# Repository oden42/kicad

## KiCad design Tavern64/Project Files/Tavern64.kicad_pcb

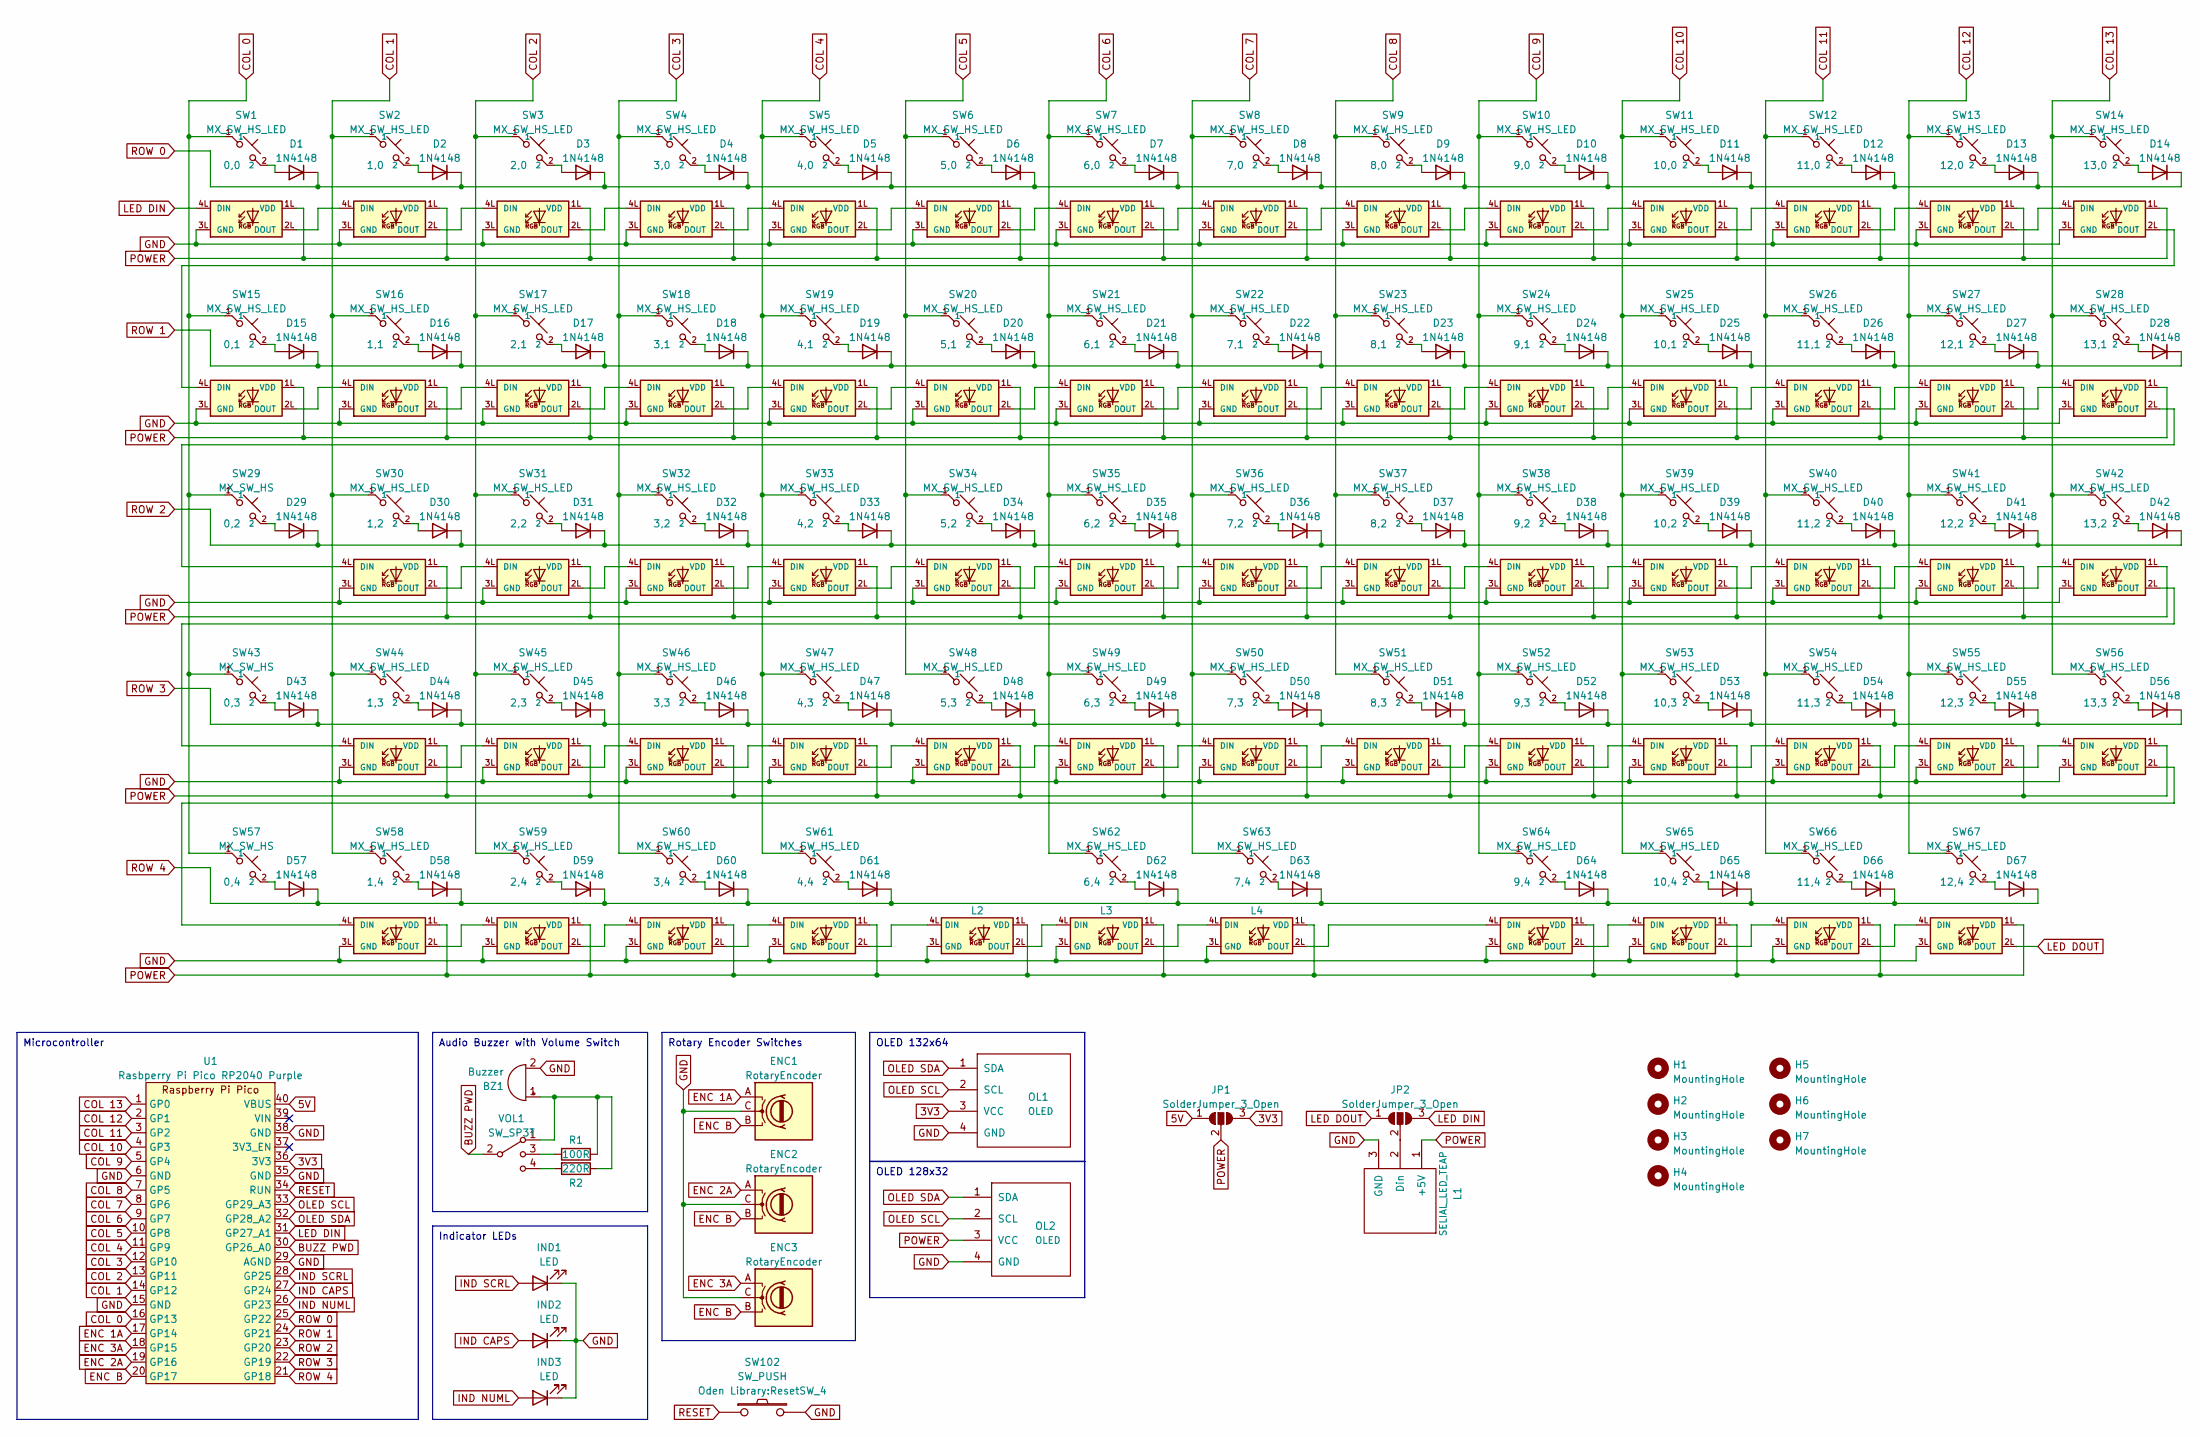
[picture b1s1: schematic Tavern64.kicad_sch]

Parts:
BZ1: Buzzer; Buzzer 8530
D1, D2, D3, D4, D5, D6, D7, D8, D9, D10, D11, D12, D13, D14, D15, D16, D17, D18, D19, D20, D21, D22, D23, D24, D25, D26, D27, D28, D29, D30, D31, D32, D33, D34, D35, D36, D37, D38, D39, D40, D41, D42, D43, D44, D45, D46, D47, D48, D49, D50, D51, D52, D53, D54, D55, D56, D57, D58, D59, D60, D61, D62, D63, D64, D65, D66, D67: 1N4148; Diode-dual
ENC1, ENC2, ENC3: RotaryEncoder; CherryMX_Choc_Hotswap v2 Encoder B
H1, H2, H3, H4, H5, H6, H7: MountingHole; MountingHole_2.2mm_M2_Pad
IND1, IND2, IND3: LED; LED_D3.0mm
JP1, JP2: SolderJumper_3_Open; SolderJumper-3_P1.3mm_Open_RoundedPad1.0x1.5mm
L1: SELIAL_LED_TEAP; SolderWire-0.127sqmm_1x03_P3.7mm_D0.48mm_OD1mm
L2, L3, L4: SK6812MINI-E
OL1: OLED; OLED 128x64 0.96 I2C Dual
OL2: OLED; OLED_v2
R1: 100R; Resistor-Hybrid
R2: 220R; Resistor-Hybrid
SW1, SW2, SW3, SW4, SW5, SW6, SW7, SW8, SW9, SW10, SW11, SW12, SW13, SW14, SW15, SW16, SW17, SW18, SW19, SW20, SW21, SW22, SW23, SW24, SW25, SW26, SW27, SW28, SW30, SW31, SW32, SW33, SW34, SW35, SW36, SW37, SW38, SW39, SW40, SW41, SW42, SW44, SW45, SW46, SW47, SW48, SW49, SW50, SW51, SW52, SW53, SW54, SW55, SW56, SW58, SW59, SW60, SW61, SW62, SW63, SW64, SW65, SW66, SW67: MX_SW_HS_LED; CherryMX_Choc_Hotswap v2 with LEDs
SW29, SW43, SW57: MX_SW_HS; CherryMX_Choc_Hotswap v2 Encoder A
SW102: SW_PUSH; ResetSW_4
U1: Rasbperry Pi Pico RP2040 Purple; Raspberry Pi Pico RP2040 Purple Reverse
VOL1: SW_SP3T; SP3T Right Angle Switch

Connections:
3V3: JP1.3 (B), OL1.3 (VCC), U1.36 (3V3)
5V: JP1.1 (A), U1.40 (VBUS)
BUZZ PWD: U1.30 (GP26_A0), VOL1.2
COL 0: SW1.1, SW15.1, SW29.1, SW43.1, SW57.1, U1.16 (GP13)
COL 1: SW2.1, SW16.1, SW30.1, SW44.1, SW58.1, U1.14 (GP12)
COL 2: SW3.1, SW17.1, SW31.1, SW45.1, SW59.1, U1.13 (GP11)
COL 3: SW4.1, SW18.1, SW32.1, SW46.1, SW60.1, U1.12 (GP10)
COL 4: SW5.1, SW19.1, SW33.1, SW47.1, SW61.1, U1.11 (GP9)
COL 5: SW6.1, SW20.1, SW34.1, SW48.1, U1.10 (GP8)
COL 6: SW7.1, SW21.1, SW35.1, SW49.1, SW62.1, U1.9 (GP7)
COL 7: SW8.1, SW22.1, SW36.1, SW50.1, SW63.1, U1.8 (GP6)
COL 8: SW9.1, SW23.1, SW37.1, SW51.1, U1.7 (GP5)
COL 9: SW10.1, SW24.1, SW38.1, SW52.1, SW64.1, U1.5 (GP4)
COL 10: SW11.1, SW25.1, SW39.1, SW53.1, SW65.1, U1.4 (GP3)
COL 11: SW12.1, SW26.1, SW40.1, SW54.1, SW66.1, U1.3 (GP2)
COL 12: SW13.1, SW27.1, SW41.1, SW55.1, SW67.1, U1.2 (GP1)
COL 13: SW14.1, SW28.1, SW42.1, SW56.1, U1.1 (GP0)
ENC 1A: ENC1.A, U1.17 (GP14)
ENC 2A: ENC2.A, U1.19 (GP16)
ENC 3A: ENC3.A, U1.18 (GP15)
ENC B: ENC1.B, ENC2.B, ENC3.B, U1.20 (GP17)
GND: BZ1.2 (+), ENC1.C, ENC2.C, ENC3.C, IND1.1 (K), IND2.1 (K), IND3.1 (K), L1.3 (GND), L2.3L (GND), L3.3L (GND), L4.3L (GND), OL1.4 (GND), OL2.4 (GND), SW1.3L (GND), SW2.3L (GND), SW3.3L (GND), SW4.3L (GND), SW5.3L (GND), SW6.3L (GND), SW7.3L (GND), SW8.3L (GND), SW9.3L (GND), SW10.3L (GND), SW11.3L (GND), SW12.3L (GND), SW13.3L (GND), SW14.3L (GND), SW15.3L (GND), SW16.3L (GND), SW17.3L (GND), SW18.3L (GND), SW19.3L (GND), SW20.3L (GND), SW21.3L (GND), SW22.3L (GND), SW23.3L (GND), SW24.3L (GND), SW25.3L (GND), SW26.3L (GND), SW27.3L (GND), SW28.3L (GND), SW30.3L (GND), SW31.3L (GND), SW32.3L (GND), SW33.3L (GND), SW34.3L (GND), SW35.3L (GND), SW36.3L (GND), SW37.3L (GND), SW38.3L (GND), SW39.3L (GND), SW40.3L (GND), SW41.3L (GND), SW42.3L (GND), SW44.3L (GND), SW45.3L (GND), SW46.3L (GND), SW47.3L (GND), SW48.3L (GND), SW49.3L (GND), SW50.3L (GND), SW51.3L (GND), SW52.3L (GND), SW53.3L (GND), SW54.3L (GND), SW55.3L (GND), SW56.3L (GND), SW58.3L (GND), SW59.3L (GND), SW60.3L (GND), SW61.3L (GND), SW64.3L (GND), SW65.3L (GND), SW66.3L (GND), SW67.3L (GND), SW102.2, U1.6 (GND), U1.15 (GND), U1.29 (AGND), U1.35 (GND), U1.38 (GND)
IND CAPS: IND2.2 (A), U1.27 (GP24)
IND NUML: IND3.2 (A), U1.26 (GP23)
IND SCRL: IND1.2 (A), U1.28 (GP25)
LED DIN: JP2.3 (B), SW1.4L (DIN), U1.31 (GP27_A1)
LED DOUT: JP2.1 (A), SW67.2L (DOUT)
unnamed: BZ1.1 (-), R1.1, R2.1, VOL1.1
unnamed: D1.2 (A), SW1.2
unnamed: D2.2 (A), SW2.2
unnamed: D3.2 (A), SW3.2
unnamed: D4.2 (A), SW4.2
unnamed: D5.2 (A), SW5.2
unnamed: D6.2 (A), SW6.2
unnamed: D7.2 (A), SW7.2
unnamed: D8.2 (A), SW8.2
unnamed: D9.2 (A), SW9.2
unnamed: D10.2 (A), SW10.2
unnamed: D11.2 (A), SW11.2
unnamed: D12.2 (A), SW12.2
unnamed: D13.2 (A), SW13.2
unnamed: D14.2 (A), SW14.2
unnamed: D15.2 (A), SW15.2
unnamed: D16.2 (A), SW16.2
unnamed: D17.2 (A), SW17.2
unnamed: D18.2 (A), SW18.2
unnamed: D19.2 (A), SW19.2
unnamed: D20.2 (A), SW20.2
unnamed: D21.2 (A), SW21.2
unnamed: D22.2 (A), SW22.2
unnamed: D23.2 (A), SW23.2
unnamed: D24.2 (A), SW24.2
unnamed: D25.2 (A), SW25.2
unnamed: D26.2 (A), SW26.2
unnamed: D27.2 (A), SW27.2
unnamed: D28.2 (A), SW28.2
unnamed: D29.2 (A), SW29.2
unnamed: D30.2 (A), SW30.2
unnamed: D31.2 (A), SW31.2
unnamed: D32.2 (A), SW32.2
unnamed: D33.2 (A), SW33.2
unnamed: D34.2 (A), SW34.2
unnamed: D35.2 (A), SW35.2
unnamed: D36.2 (A), SW36.2
unnamed: D37.2 (A), SW37.2
unnamed: D38.2 (A), SW38.2
unnamed: D39.2 (A), SW39.2
unnamed: D40.2 (A), SW40.2
unnamed: D41.2 (A), SW41.2
unnamed: D42.2 (A), SW42.2
unnamed: D43.2 (A), SW43.2
unnamed: D44.2 (A), SW44.2
unnamed: D45.2 (A), SW45.2
unnamed: D46.2 (A), SW46.2
unnamed: D47.2 (A), SW47.2
unnamed: D48.2 (A), SW48.2
unnamed: D49.2 (A), SW49.2
unnamed: D50.2 (A), SW50.2
unnamed: D51.2 (A), SW51.2
unnamed: D52.2 (A), SW52.2
unnamed: D53.2 (A), SW53.2
unnamed: D54.2 (A), SW54.2
unnamed: D55.2 (A), SW55.2
unnamed: D56.2 (A), SW56.2
unnamed: D57.2 (A), SW57.2
unnamed: D58.2 (A), SW58.2
unnamed: D59.2 (A), SW59.2
unnamed: D60.2 (A), SW60.2
unnamed: D61.2 (A), SW61.2
unnamed: D62.2 (A), SW62.2
unnamed: D63.2 (A), SW63.2
unnamed: D64.2 (A), SW64.2
unnamed: D65.2 (A), SW65.2
unnamed: D66.2 (A), SW66.2
unnamed: D67.2 (A), SW67.2
unnamed: JP2.2 (C), L1.2 (Din)
unnamed: L2.4L (DIN), SW61.2L (DOUT)
unnamed: L2.2L (DOUT), L3.4L (DIN)
unnamed: L3.2L (DOUT), L4.4L (DIN)
unnamed: L4.2L (DOUT), SW64.4L (DIN)
unnamed: R1.2, VOL1.3
unnamed: R2.2, VOL1.4
unnamed: SW1.2L (DOUT), SW2.4L (DIN)
unnamed: SW2.2L (DOUT), SW3.4L (DIN)
unnamed: SW3.2L (DOUT), SW4.4L (DIN)
unnamed: SW4.2L (DOUT), SW5.4L (DIN)
unnamed: SW5.2L (DOUT), SW6.4L (DIN)
unnamed: SW6.2L (DOUT), SW7.4L (DIN)
unnamed: SW7.2L (DOUT), SW8.4L (DIN)
unnamed: SW8.2L (DOUT), SW9.4L (DIN)
unnamed: SW9.2L (DOUT), SW10.4L (DIN)
unnamed: SW10.2L (DOUT), SW11.4L (DIN)
unnamed: SW11.2L (DOUT), SW12.4L (DIN)
unnamed: SW12.2L (DOUT), SW13.4L (DIN)
unnamed: SW13.2L (DOUT), SW14.4L (DIN)
unnamed: SW14.2L (DOUT), SW15.4L (DIN)
unnamed: SW15.2L (DOUT), SW16.4L (DIN)
unnamed: SW16.2L (DOUT), SW17.4L (DIN)
unnamed: SW17.2L (DOUT), SW18.4L (DIN)
unnamed: SW18.2L (DOUT), SW19.4L (DIN)
unnamed: SW19.2L (DOUT), SW20.4L (DIN)
unnamed: SW20.2L (DOUT), SW21.4L (DIN)
unnamed: SW21.2L (DOUT), SW22.4L (DIN)
unnamed: SW22.2L (DOUT), SW23.4L (DIN)
unnamed: SW23.2L (DOUT), SW24.4L (DIN)
unnamed: SW24.2L (DOUT), SW25.4L (DIN)
unnamed: SW25.2L (DOUT), SW26.4L (DIN)
unnamed: SW26.2L (DOUT), SW27.4L (DIN)
unnamed: SW27.2L (DOUT), SW28.4L (DIN)
unnamed: SW28.2L (DOUT), SW30.4L (DIN)
unnamed: SW30.2L (DOUT), SW31.4L (DIN)
unnamed: SW31.2L (DOUT), SW32.4L (DIN)
unnamed: SW32.2L (DOUT), SW33.4L (DIN)
unnamed: SW33.2L (DOUT), SW34.4L (DIN)
unnamed: SW34.2L (DOUT), SW35.4L (DIN)
unnamed: SW35.2L (DOUT), SW36.4L (DIN)
unnamed: SW36.2L (DOUT), SW37.4L (DIN)
unnamed: SW37.2L (DOUT), SW38.4L (DIN)
unnamed: SW38.2L (DOUT), SW39.4L (DIN)
unnamed: SW39.2L (DOUT), SW40.4L (DIN)
unnamed: SW40.2L (DOUT), SW41.4L (DIN)
unnamed: SW41.2L (DOUT), SW42.4L (DIN)
unnamed: SW42.2L (DOUT), SW44.4L (DIN)
unnamed: SW44.2L (DOUT), SW45.4L (DIN)
unnamed: SW45.2L (DOUT), SW46.4L (DIN)
unnamed: SW46.2L (DOUT), SW47.4L (DIN)
unnamed: SW47.2L (DOUT), SW48.4L (DIN)
unnamed: SW48.2L (DOUT), SW49.4L (DIN)
unnamed: SW49.2L (DOUT), SW50.4L (DIN)
unnamed: SW50.2L (DOUT), SW51.4L (DIN)
unnamed: SW51.2L (DOUT), SW52.4L (DIN)
unnamed: SW52.2L (DOUT), SW53.4L (DIN)
unnamed: SW53.2L (DOUT), SW54.4L (DIN)
unnamed: SW54.2L (DOUT), SW55.4L (DIN)
unnamed: SW55.2L (DOUT), SW56.4L (DIN)
unnamed: SW56.2L (DOUT), SW58.4L (DIN)
unnamed: SW58.2L (DOUT), SW59.4L (DIN)
unnamed: SW59.2L (DOUT), SW60.4L (DIN)
unnamed: SW60.2L (DOUT), SW61.4L (DIN)
unnamed: SW64.2L (DOUT), SW65.4L (DIN)
unnamed: SW65.2L (DOUT), SW66.4L (DIN)
unnamed: SW66.2L (DOUT), SW67.4L (DIN)
OLED SCL: OL1.2 (SCL), OL2.2 (SCL), U1.33 (GP29_A3)
OLED SDA: OL1.1 (SDA), OL2.1 (SDA), U1.32 (GP28_A2)
POWER: JP1.2 (C), L1.1 (+5V), L2.1L (VDD), L3.1L (VDD), L4.1L (VDD), OL2.3 (VCC), SW1.1L (VDD), SW2.1L (VDD), SW3.1L (VDD), SW4.1L (VDD), SW5.1L (VDD), SW6.1L (VDD), SW7.1L (VDD), SW8.1L (VDD), SW9.1L (VDD), SW10.1L (VDD), SW11.1L (VDD), SW12.1L (VDD), SW13.1L (VDD), SW14.1L (VDD), SW15.1L (VDD), SW16.1L (VDD), SW17.1L (VDD), SW18.1L (VDD), SW19.1L (VDD), SW20.1L (VDD), SW21.1L (VDD), SW22.1L (VDD), SW23.1L (VDD), SW24.1L (VDD), SW25.1L (VDD), SW26.1L (VDD), SW27.1L (VDD), SW28.1L (VDD), SW30.1L (VDD), SW31.1L (VDD), SW32.1L (VDD), SW33.1L (VDD), SW34.1L (VDD), SW35.1L (VDD), SW36.1L (VDD), SW37.1L (VDD), SW38.1L (VDD), SW39.1L (VDD), SW40.1L (VDD), SW41.1L (VDD), SW42.1L (VDD), SW44.1L (VDD), SW45.1L (VDD), SW46.1L (VDD), SW47.1L (VDD), SW48.1L (VDD), SW49.1L (VDD), SW50.1L (VDD), SW51.1L (VDD), SW52.1L (VDD), SW53.1L (VDD), SW54.1L (VDD), SW55.1L (VDD), SW56.1L (VDD), SW58.1L (VDD), SW59.1L (VDD), SW60.1L (VDD), SW61.1L (VDD), SW64.1L (VDD), SW65.1L (VDD), SW66.1L (VDD), SW67.1L (VDD)
RESET: SW102.1, U1.34 (RUN)
ROW 0: D1.1 (K), D2.1 (K), D3.1 (K), D4.1 (K), D5.1 (K), D6.1 (K), D7.1 (K), D8.1 (K), D9.1 (K), D10.1 (K), D11.1 (K), D12.1 (K), D13.1 (K), D14.1 (K), U1.25 (GP22)
ROW 1: D15.1 (K), D16.1 (K), D17.1 (K), D18.1 (K), D19.1 (K), D20.1 (K), D21.1 (K), D22.1 (K), D23.1 (K), D24.1 (K), D25.1 (K), D26.1 (K), D27.1 (K), D28.1 (K), U1.24 (GP21)
ROW 2: D29.1 (K), D30.1 (K), D31.1 (K), D32.1 (K), D33.1 (K), D34.1 (K), D35.1 (K), D36.1 (K), D37.1 (K), D38.1 (K), D39.1 (K), D40.1 (K), D41.1 (K), D42.1 (K), U1.23 (GP20)
ROW 3: D43.1 (K), D44.1 (K), D45.1 (K), D46.1 (K), D47.1 (K), D48.1 (K), D49.1 (K), D50.1 (K), D51.1 (K), D52.1 (K), D53.1 (K), D54.1 (K), D55.1 (K), D56.1 (K), U1.22 (GP19)
ROW 4: D57.1 (K), D58.1 (K), D59.1 (K), D60.1 (K), D61.1 (K), D62.1 (K), D63.1 (K), D64.1 (K), D65.1 (K), D66.1 (K), D67.1 (K), U1.21 (GP18)

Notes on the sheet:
Indicator LEDs
Audio Buzzer with Volume Switch
Rotary Encoder Switches
OLED 128x32
OLED 132x64
Microcontroller

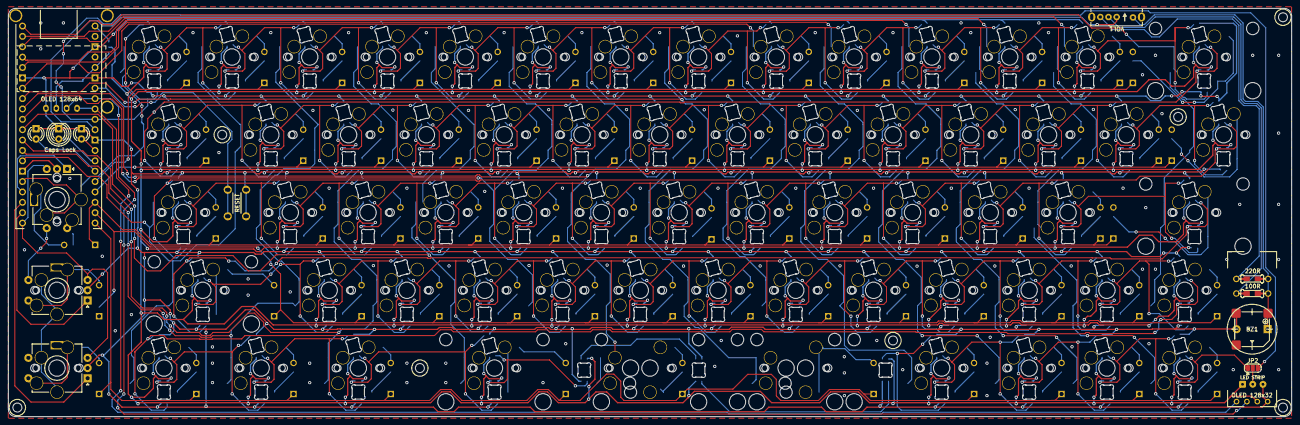
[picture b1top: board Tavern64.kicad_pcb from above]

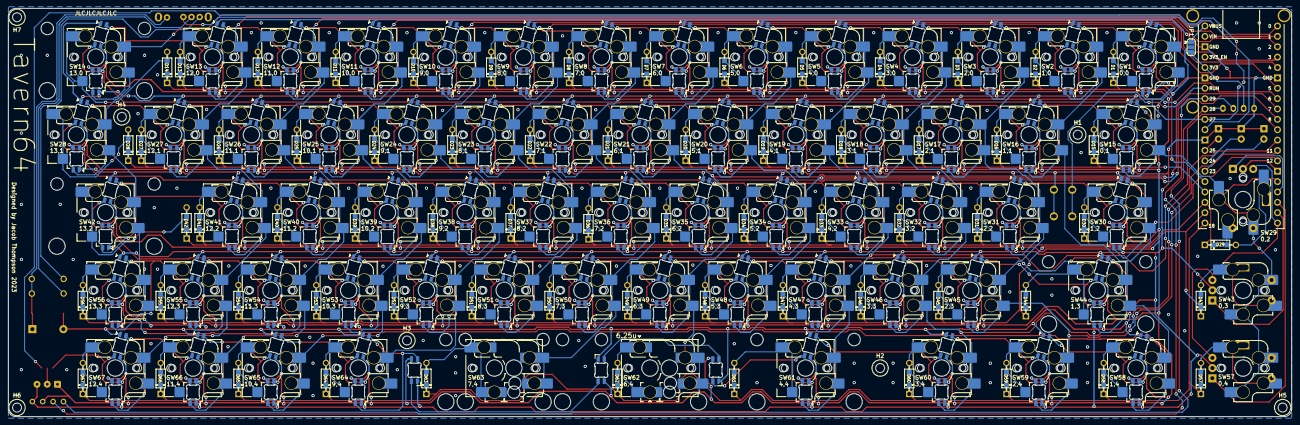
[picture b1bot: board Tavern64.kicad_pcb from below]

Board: 2 copper layers, 314.3 x 100.0 mm, 161 parts (75 on the bottom side), 171 nets.

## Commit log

2023-05-18 Rename Tavern64.kicad_sch to Tavern64/Project Files/Tavern64.kicad_sch
2023-05-18 Rename Tavern64.kicad_pro to Tavern64/Project Files/Tavern64.kicad_pro
2023-05-18 Move files to new directory
2023-05-18 Rename images
